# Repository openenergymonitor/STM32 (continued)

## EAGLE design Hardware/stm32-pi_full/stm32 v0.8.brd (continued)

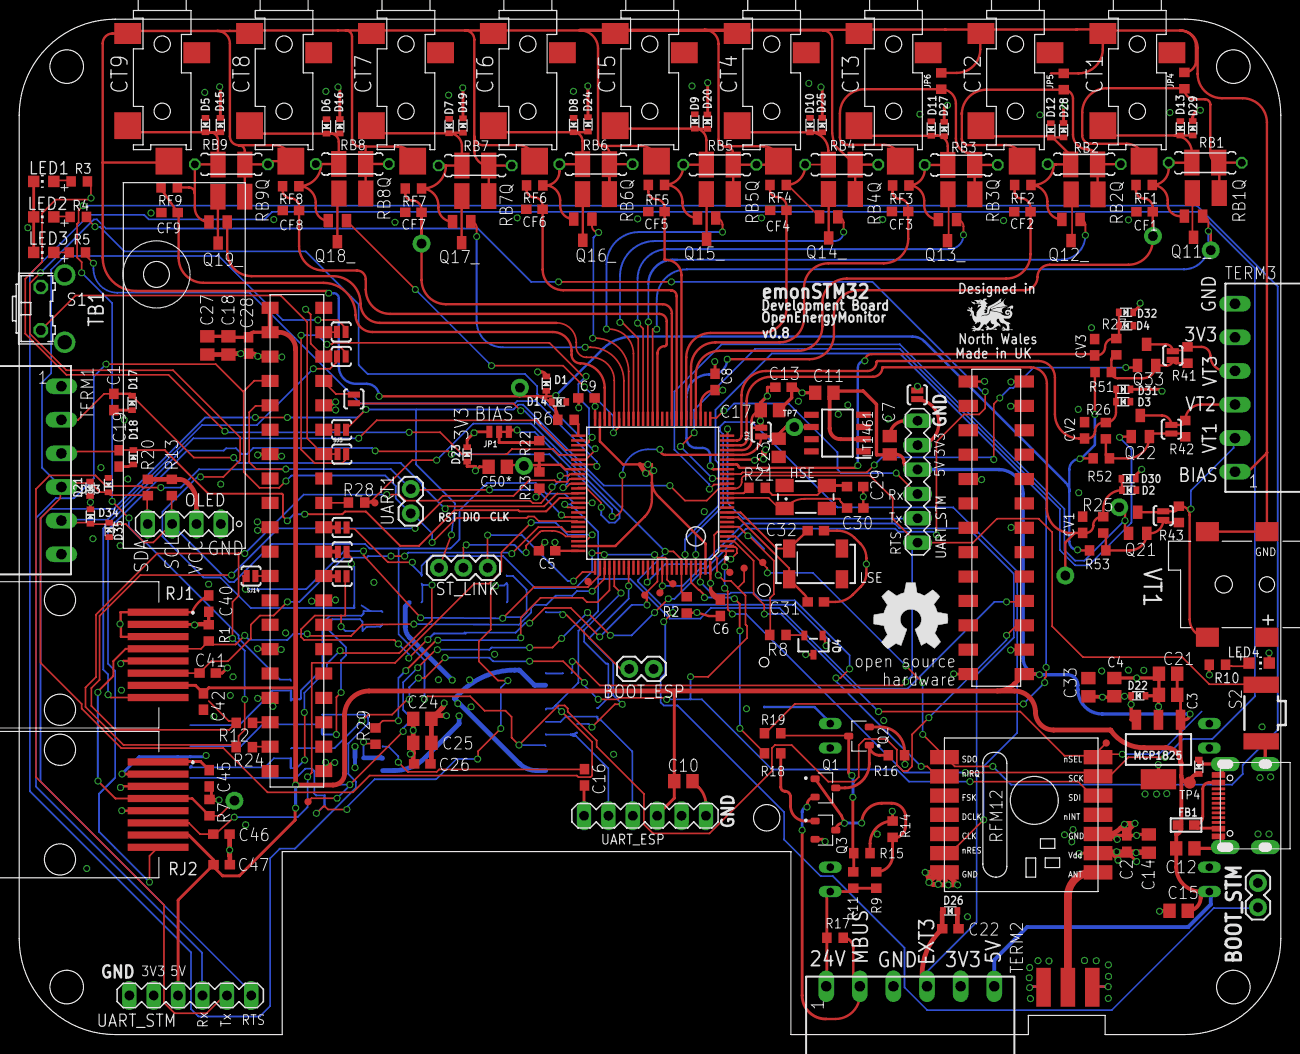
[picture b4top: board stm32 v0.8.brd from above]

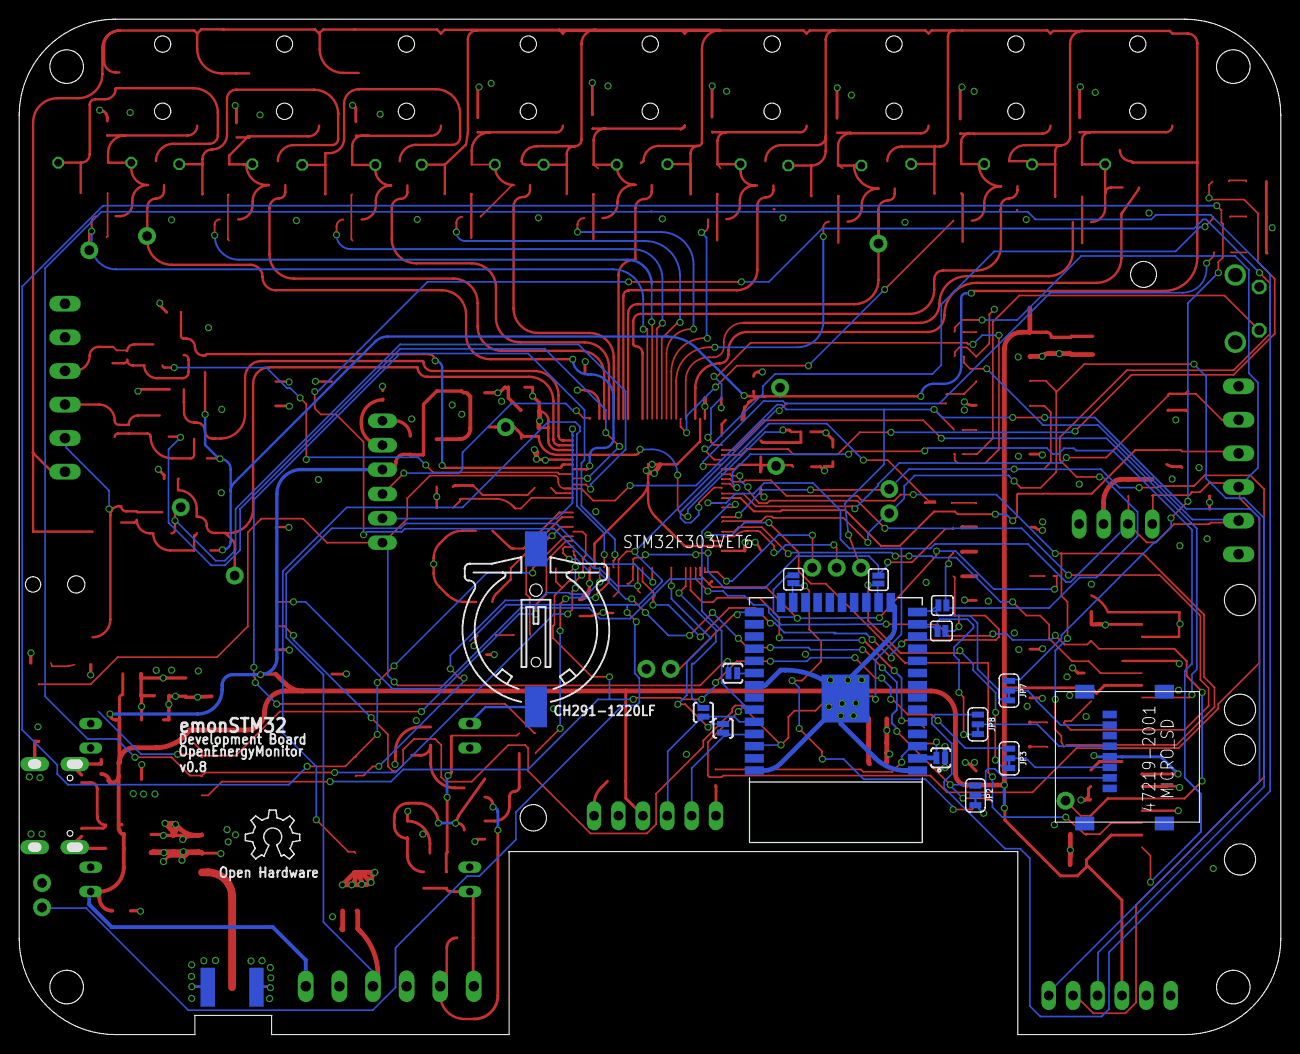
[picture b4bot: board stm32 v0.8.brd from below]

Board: 4 copper layers, 131.4 x 105.8 mm, 270 parts (16 on the bottom side), 147 nets.

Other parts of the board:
LOGO1: OSHW_LOGO_6MILX0200-NT; OSHW_6X200_NOTEXT

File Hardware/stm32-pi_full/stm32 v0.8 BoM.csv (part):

Part;Value;Device;Package;Description;ALLIED_NUMBER;ALLIED_PRICE-STOCK;AVAILABILITY;CREATED_BY;DESCRIPTION;DIGIKEY_PART_NUMBER;HEIGHT;MANUFACTURER;MANUFACTURER_NAME;MANUFACTURER_PART_NUMBER;MF;MOUSER_PART_NUMBER;MOUSER_PRICE-STOCK;MP;MPN;OC_FARNELL;OC_NEWARK;PACKAGE;POPULARITY;PRICE;PROD_ID;RS_PART_NUMBER;RS_PRICE-STOCK;SPICEPREFIX;TP_SIGNAL_NAME;VALUE
BOOT_ESP;;M02PTH;1X02;Header 2;;;;;;;;;;;;;;;;;;;;;;;;;;
BOOT_STM;;M02PTH;1X02;Header 2;;;;;;;;;;;;;;;;;;;;;;;;;;
C1;100nF;C-EUC0603;C0603;CAPACITOR, European symbol;;;;;;;;;;;;;;;;;;;;;;;;;;
C2;100nF;C-EUC0603;C0603;CAPACITOR, European symbol;;;;;;;;;;;;;;;;;;;;;;;;;;
C3;2.2uF;C-EUC0805;C0805;CAPACITOR, European symbol;;;;;;;;;;;;;;;;;;;88;;;;;C;;
C4;2.2uF;C-EUC0805;C0805;CAPACITOR, European symbol;;;;;;;;;;;;;;;;;;;88;;;;;C;;
C5;100nF;C-EUC0603;C0603;CAPACITOR, European symbol;;;;;;;;;;;;;;;;;;;;;;;;;;
C6;100nF;C-EUC0603;C0603;CAPACITOR, European symbol;;;;;;;;;;;;;;;;;;;;;;;;;;
C7;2.2uF;C-EUC0805;C0805;CAPACITOR, European symbol;;;;;;;;;;;;;;;;;;;88;;;;;C;;
C8;100nF;C-EUC0603;C0603;CAPACITOR, European symbol;;;;;;;;;;;;;;;;;;;;;;;;;;
C9;100nF;C-EUC0603;C0603;CAPACITOR, European symbol;;;;;;;;;;;;;;;;;;;;;;;;;;
C10;2.2uF;C-EUC0805;C0805;CAPACITOR, European symbol;;;;;;;;;;;;;;;;;;;88;;;;;C;;
C11;2.2uF;C-EUC0805;C0805;CAPACITOR, European symbol;;;;;;;;;;;;;;;;;;;88;;;;;C;;
C12;47uF;C-EUC0805;C0805;CAPACITOR, European symbol;;;;;;;;;;;;;;;;;;;88;;;;;C;;
C13;100nF;C-EUC0603;C0603;CAPACITOR, European symbol;;;;;;;;;;;;;;;;;;;73;;;;;C;;
C14;2.2uF;C-EUC0805;C0805;CAPACITOR, European symbol;;;;;;;;;;;;;;;;;;;88;;;;;C;;
C15;2.2uF;C-EUC0805;C0805;CAPACITOR, European symbol;;;;;;;;;;;;;;;;;;;88;;;;;C;;
C16;100nF;C-EUC0603;C0603;CAPACITOR, European symbol;;;;;;;;;;;;;;;;;;;;;;;;;;
C17;2.2uF;C-EUC0805;C0805;CAPACITOR, European symbol;;;;;;;;;;;;;;;;;;;88;;;;;C;;
C18;2.2uF;C-EUC0805;C0805;CAPACITOR, European symbol;;;;;;;;;;;;;;;;;;;88;;;;;C;;
C19;100nF;C-EUC0603;C0603;CAPACITOR, European symbol;;;;;;;;;;;;;;;;;;;;;;;;;;
C21;47uF;C-EUC0805;C0805;CAPACITOR, European symbol;;;;;;;;;;;;;;;;;;;88;;;;;C;;
C22;100nF;C-EUC0603;C0603;CAPACITOR, European symbol;;;;;;;;;;;;;;;;;;;;;;;;;;
C23;2.2uF;C-EUC0805;C0805;CAPACITOR, European symbol;;;;;;;;;;;;;;;;;;;88;;;;;C;;
C24;2.2uF;C-EUC0805;C0805;CAPACITOR, European symbol;;;;;;;;;;;;;;;;;;;88;;;;;C;;
C25;2.2uF;C-EUC0805;C0805;CAPACITOR, European symbol;;;;;;;;;;;;;;;;;;;88;;;;;C;;
C26;100nF;C-EUC0603;C0603;CAPACITOR, European symbol;;;;;;;;;;;;;;;;;;;;;;;;;;
C27;2.2uF;C-EUC0805;C0805;CAPACITOR, European symbol;;;;;;;;;;;;;;;;;;;88;;;;;C;;
C28;100nF;C-EUC0603;C0603;CAPACITOR, European symbol;;;;;;;;;;;;;;;;;;;;;;;;;;
C29;15pF;C-EUC0603;C0603;CAPACITOR, European symbol;;;;;;;;;;;;;;;;;;;73;;;;;C;;
C30;15pF;C-EUC0603;C0603;CAPACITOR, European symbol;;;;;;;;;;;;;;;;;;;73;;;;;C;;
C31;10pF;C-EUC0603;C0603;CAPACITOR, European symbol;;;;;;;;;;;;;;;;;;;88;;;;;C;;
C32;10pF;C-EUC0603;C0603;CAPACITOR, European symbol;;;;;;;;;;;;;;;;;;;88;;;;;C;;
C33;47uF;C-EUC0805;C0805;CAPACITOR, European symbol;;;;;;;;;;;;;;;;;;;88;;;;;C;;
C40;100nF;C-EUC0603;C0603;CAPACITOR, European symbol;;;;;;;;;;;;;;;;;;;;;;;;;;
C41;100nF;C-EUC0603;C0603;CAPACITOR, European symbol;;;;;;;;;;;;;;;;;;;;;;;;;;
C42;100nF;C-EUC0603;C0603;CAPACITOR, European symbol;;;;;;;;;;;;;;;;;;;;;;;;;;
C45;100nF;C-EUC0603;C0603;CAPACITOR, European symbol;;;;;;;;;;;;;;;;;;;;;;;;;;
C46;100nF;C-EUC0603;C0603;CAPACITOR, European symbol;;;;;;;;;;;;;;;;;;;;;;;;;;
C47;100nF;C-EUC0603;C0603;CAPACITOR, European symbol;;;;;;;;;;;;;;;;;;;;;;;;;;
C50*;2.2uF;C-EUC0805;C0805;CAPACITOR, European symbol;;;;;;;;;;;;;;;;;;;88;;;;;C;;
CF1;10nF;C-EUC0805;C0805;CAPACITOR, European symbol;;;;;;;;;;;;;;;;;;;;;;;;;;
CF2;10nF;C-EUC0805;C0805;CAPACITOR, European symbol;;;;;;;;;;;;;;;;;;;;;;;;;;
CF3;10nF;C-EUC0805;C0805;CAPACITOR, European symbol;;;;;;;;;;;;;;;;;;;;;;;;;;
CF4;10nF;C-EUC0805;C0805;CAPACITOR, European symbol;;;;;;;;;;;;;;;;;;;;;;;;;;
CF5;10nF;C-EUC0805;C0805;CAPACITOR, European symbol;;;;;;;;;;;;;;;;;;;;;;;;;;
CF6;10nF;C-EUC0805;C0805;CAPACITOR, European symbol;;;;;;;;;;;;;;;;;;;;;;;;;;
CF7;10nF;C-EUC0805;C0805;CAPACITOR, European symbol;;;;;;;;;;;;;;;;;;;;;;;;;;
CF8;10nF;C-EUC0805;C0805;CAPACITOR, European symbol;;;;;;;;;;;;;;;;;;;;;;;;;;
CF9;10nF;C-EUC0805;C0805;CAPACITOR, European symbol;;;;;;;;;;;;;;;;;;;;;;;;;;
CT1;SJ-3523-SMT;STEREO_SMD;STEREO_SMT;3.5mm Stereo Jack SMT;;;;;;;;;;;;;;;SJ-3523-SMT;;;;;;;;;;;
CT2;SJ-3523-SMT;STEREO_SMD;STEREO_SMT;3.5mm Stereo Jack SMT;;;;;;;;;;;;;;;SJ-3523-SMT;;;;;;;;;;;
CT3;SJ-3523-SMT;STEREO_SMD;STEREO_SMT;3.5mm Stereo Jack SMT;;;;;;;;;;;;;;;SJ-3523-SMT;;;;;;;;;;;
CT4;SJ-3523-SMT;STEREO_SMD;STEREO_SMT;3.5mm Stereo Jack SMT;;;;;;;;;;;;;;;SJ-3523-SMT;;;;;;;;;;;
CT5;SJ-3523-SMT;STEREO_SMD;STEREO_SMT;3.5mm Stereo Jack SMT;;;;;;;;;;;;;;;SJ-3523-SMT;;;;;;;;;;;
CT6;SJ-3523-SMT;STEREO_SMD;STEREO_SMT;3.5mm Stereo Jack SMT;;;;;;;;;;;;;;;SJ-3523-SMT;;;;;;;;;;;
CT7;SJ-3523-SMT;STEREO_SMD;STEREO_SMT;3.5mm Stereo Jack SMT;;;;;;;;;;;;;;;SJ-3523-SMT;;;;;;;;;;;
CT8;SJ-3523-SMT;STEREO_SMD;STEREO_SMT;3.5mm Stereo Jack SMT;;;;;;;;;;;;;;;SJ-3523-SMT;;;;;;;;;;;
CT9;SJ-3523-SMT;STEREO_SMD;STEREO_SMT;3.5mm Stereo Jack SMT;;;;;;;;;;;;;;;SJ-3523-SMT;;;;;;;;;;;
CV1;10nF;C-EUC0805;C0805;CAPACITOR, European symbol;;;;;;;;;;;;;;;;;;;;;;;;;;
CV2;10nF;C-EUC0805;C0805;CAPACITOR, European symbol;;;;;;;;;;;;;;;;;;;;;;;;;;
CV3;10nF;C-EUC0805;C0805;CAPACITOR, European symbol;;;;;;;;;;;;;;;;;;;;;;;;;;
D1;ESD5Z3.3T1G;DIODESOD-523;SOD-523;Diode;;;;;;;;;;;;;;;;;;;;;;;;;;
D2;ESD5Z3.3T1G;DIODESOD-523;SOD-523;Diode;;;;;;;;;;;;;;;;;;;;;;;;;;
D3;ESD5Z3.3T1G;DIODESOD-523;SOD-523;Diode;;;;;;;;;;;;;;;;;;;;;;;;;;
D4;ESD5Z3.3T1G;DIODESOD-523;SOD-523;Diode;;;;;;;;;;;;;;;;;;;;;;;;;;
D5;ESD5Z3.3T1G;DIODESOD-523;SOD-523;Diode;;;;;;;;;;;;;;;;;;;;;;;;;;
D6;ESD5Z3.3T1G;DIODESOD-523;SOD-523;Diode;;;;;;;;;;;;;;;;;;;;;;;;;;
D7;ESD5Z3.3T1G;DIODESOD-523;SOD-523;Diode;;;;;;;;;;;;;;;;;;;;;;;;;;
D8;ESD5Z3.3T1G;DIODESOD-523;SOD-523;Diode;;;;;;;;;;;;;;;;;;;;;;;;;;
D9;ESD5Z3.3T1G;DIODESOD-523;SOD-523;Diode;;;;;;;;;;;;;;;;;;;;;;;;;;
D10;ESD5Z3.3T1G;DIODESOD-523;SOD-523;Diode;;;;;;;;;;;;;;;;;;;;;;;;;;
D11;ESD5Z3.3T1G;DIODESOD-523;SOD-523;Diode;;;;;;;;;;;;;;;;;;;;;;;;;;
D12;ESD5Z3.3T1G;DIODESOD-523;SOD-523;Diode;;;;;;;;;;;;;;;;;;;;;;;;;;
D13;ESD5Z3.3T1G;DIODESOD-523;SOD-523;Diode;;;;;;;;;;;;;;;;;;;;;;;;;;
D14;ESD5Z3.3T1G;DIODESOD-523;SOD-523;Diode;;;;;;;;;;;;;;;;;;;;;;;;;;
D15;ESD5Z3.3T1G;DIODESOD-523;SOD-523;Diode;;;;;;;;;;;;;;;;;;;;;;;;;;
D16;ESD5Z3.3T1G;DIODESOD-523;SOD-523;Diode;;;;;;;;;;;;;;;;;;;;;;;;;;
D17;ESD5Z3.3T1G;DIODESOD-523;SOD-523;Diode;;;;;;;;;;;;;;;;;;;;;;;;;;
D18;ESD5Z3.3T1G;DIODESOD-523;SOD-523;Diode;;;;;;;;;;;;;;;;;;;;;;;;;;
D19;ESD5Z3.3T1G;DIODESOD-523;SOD-523;Diode;;;;;;;;;;;;;;;;;;;;;;;;;;
D20;ESD5Z3.3T1G;DIODESOD-523;SOD-523;Diode;;;;;;;;;;;;;;;;;;;;;;;;;;
D21;ESD5Z3.3T1G;DIODESOD-523;SOD-523;Diode;;;;;;;;;;;;;;;;;;;;;;;;;;
D22;ESD5Z3.3T1G;DIODESOD-523;SOD-523;Diode;;;;;;;;;;;;;;;;;;;;;;;;;;
D23;ESD5Z3.3T1G;DIODESOD-523;SOD-523;Diode;;;;;;;;;;;;;;;;;;;;;;;;;;
D24;ESD5Z3.3T1G;DIODESOD-523;SOD-523;Diode;;;;;;;;;;;;;;;;;;;;;;;;;;
D25;ESD5Z3.3T1G;DIODESOD-523;SOD-523;Diode;;;;;;;;;;;;;;;;;;;;;;;;;;
D26;ESD5Z3.3T1G;DIODESOD-523;SOD-523;Diode;;;;;;;;;;;;;;;;;;;;;;;;;;
D27;ESD5Z3.3T1G;DIODESOD-523;SOD-523;Diode;;;;;;;;;;;;;;;;;;;;;;;;;;
D28;ESD5Z3.3T1G;DIODESOD-523;SOD-523;Diode;;;;;;;;;;;;;;;;;;;;;;;;;;
D29;ESD5Z3.3T1G;DIODESOD-523;SOD-523;Diode;;;;;;;;;;;;;;;;;;;;;;;;;;
D30;ESD5Z3.3T1G;DIODESOD-523;SOD-523;Diode;;;;;;;;;;;;;;;;;;;;;;;;;;
D31;ESD5Z3.3T1G;DIODESOD-523;SOD-523;Diode;;;;;;;;;;;;;;;;;;;;;;;;;;
D32;ESD5Z3.3T1G;DIODESOD-523;SOD-523;Diode;;;;;;;;;;;;;;;;;;;;;;;;;;
D33;ESD5Z3.3T1G;DIODESOD-523;SOD-523;Diode;;;;;;;;;;;;;;;;;;;;;;;;;;
D34;ESD5Z3.3T1G;DIODESOD-523;SOD-523;Diode;;;;;;;;;;;;;;;;;;;;;;;;;;
D35;ESD5Z3.3T1G;DIODESOD-523;SOD-523;Diode;;;;;;;;;;;;;;;;;;;;;;;;;;
D40*1;ESD5Z5.0T1G;DIODESOD-523;SOD-523;Diode;;;;;;;;;;;;;;;;;;;;;;;;;;
EXPANSION;TSM-113-01-T-DV;PINHD-2X13SMT;2X13_SMT;PIN HEADER;;;;;;;;;;;;;;;;;;;;;;;;;;
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
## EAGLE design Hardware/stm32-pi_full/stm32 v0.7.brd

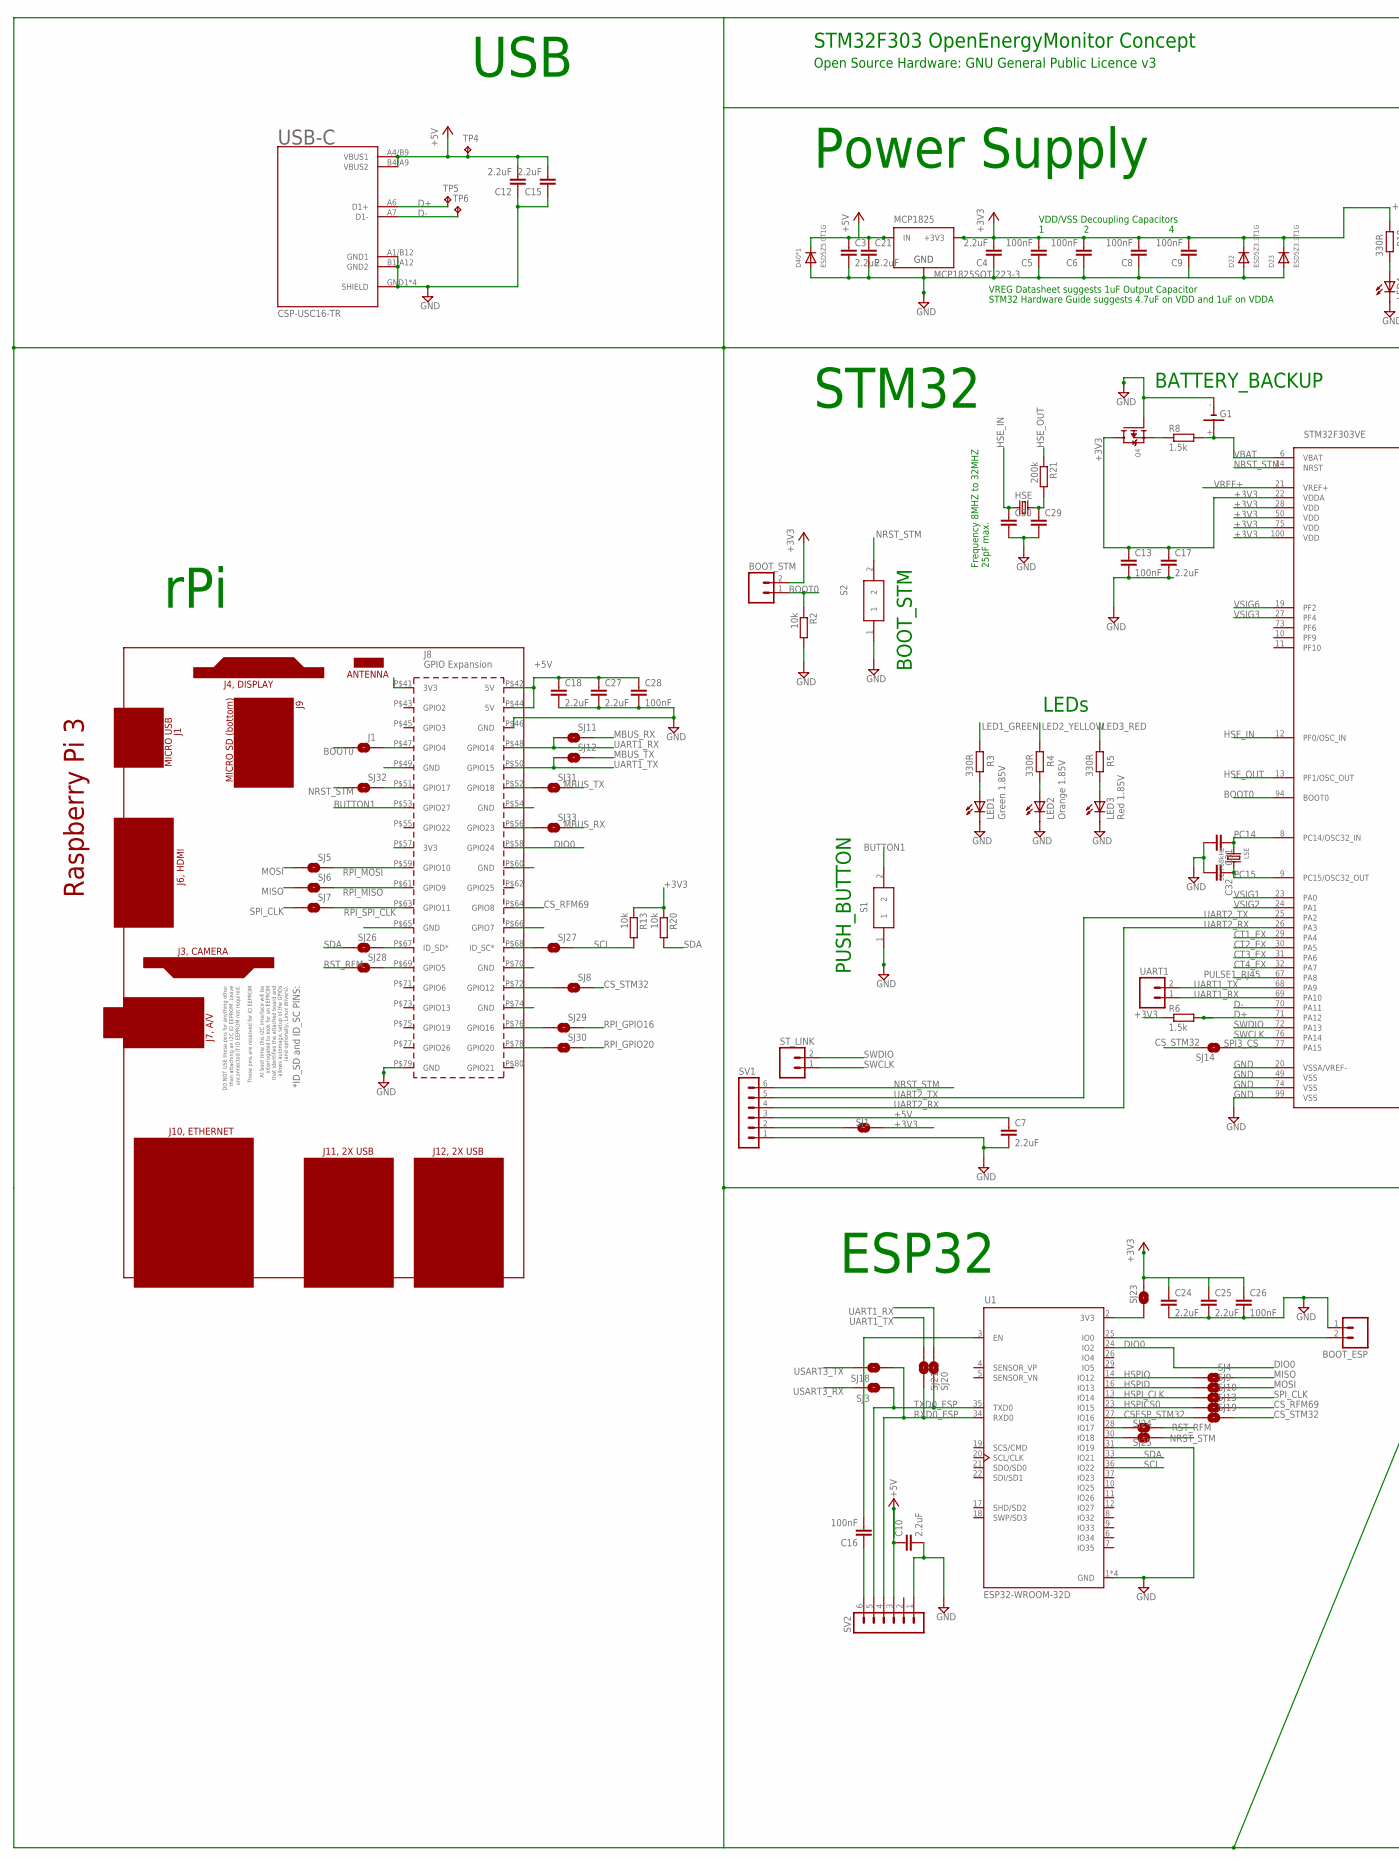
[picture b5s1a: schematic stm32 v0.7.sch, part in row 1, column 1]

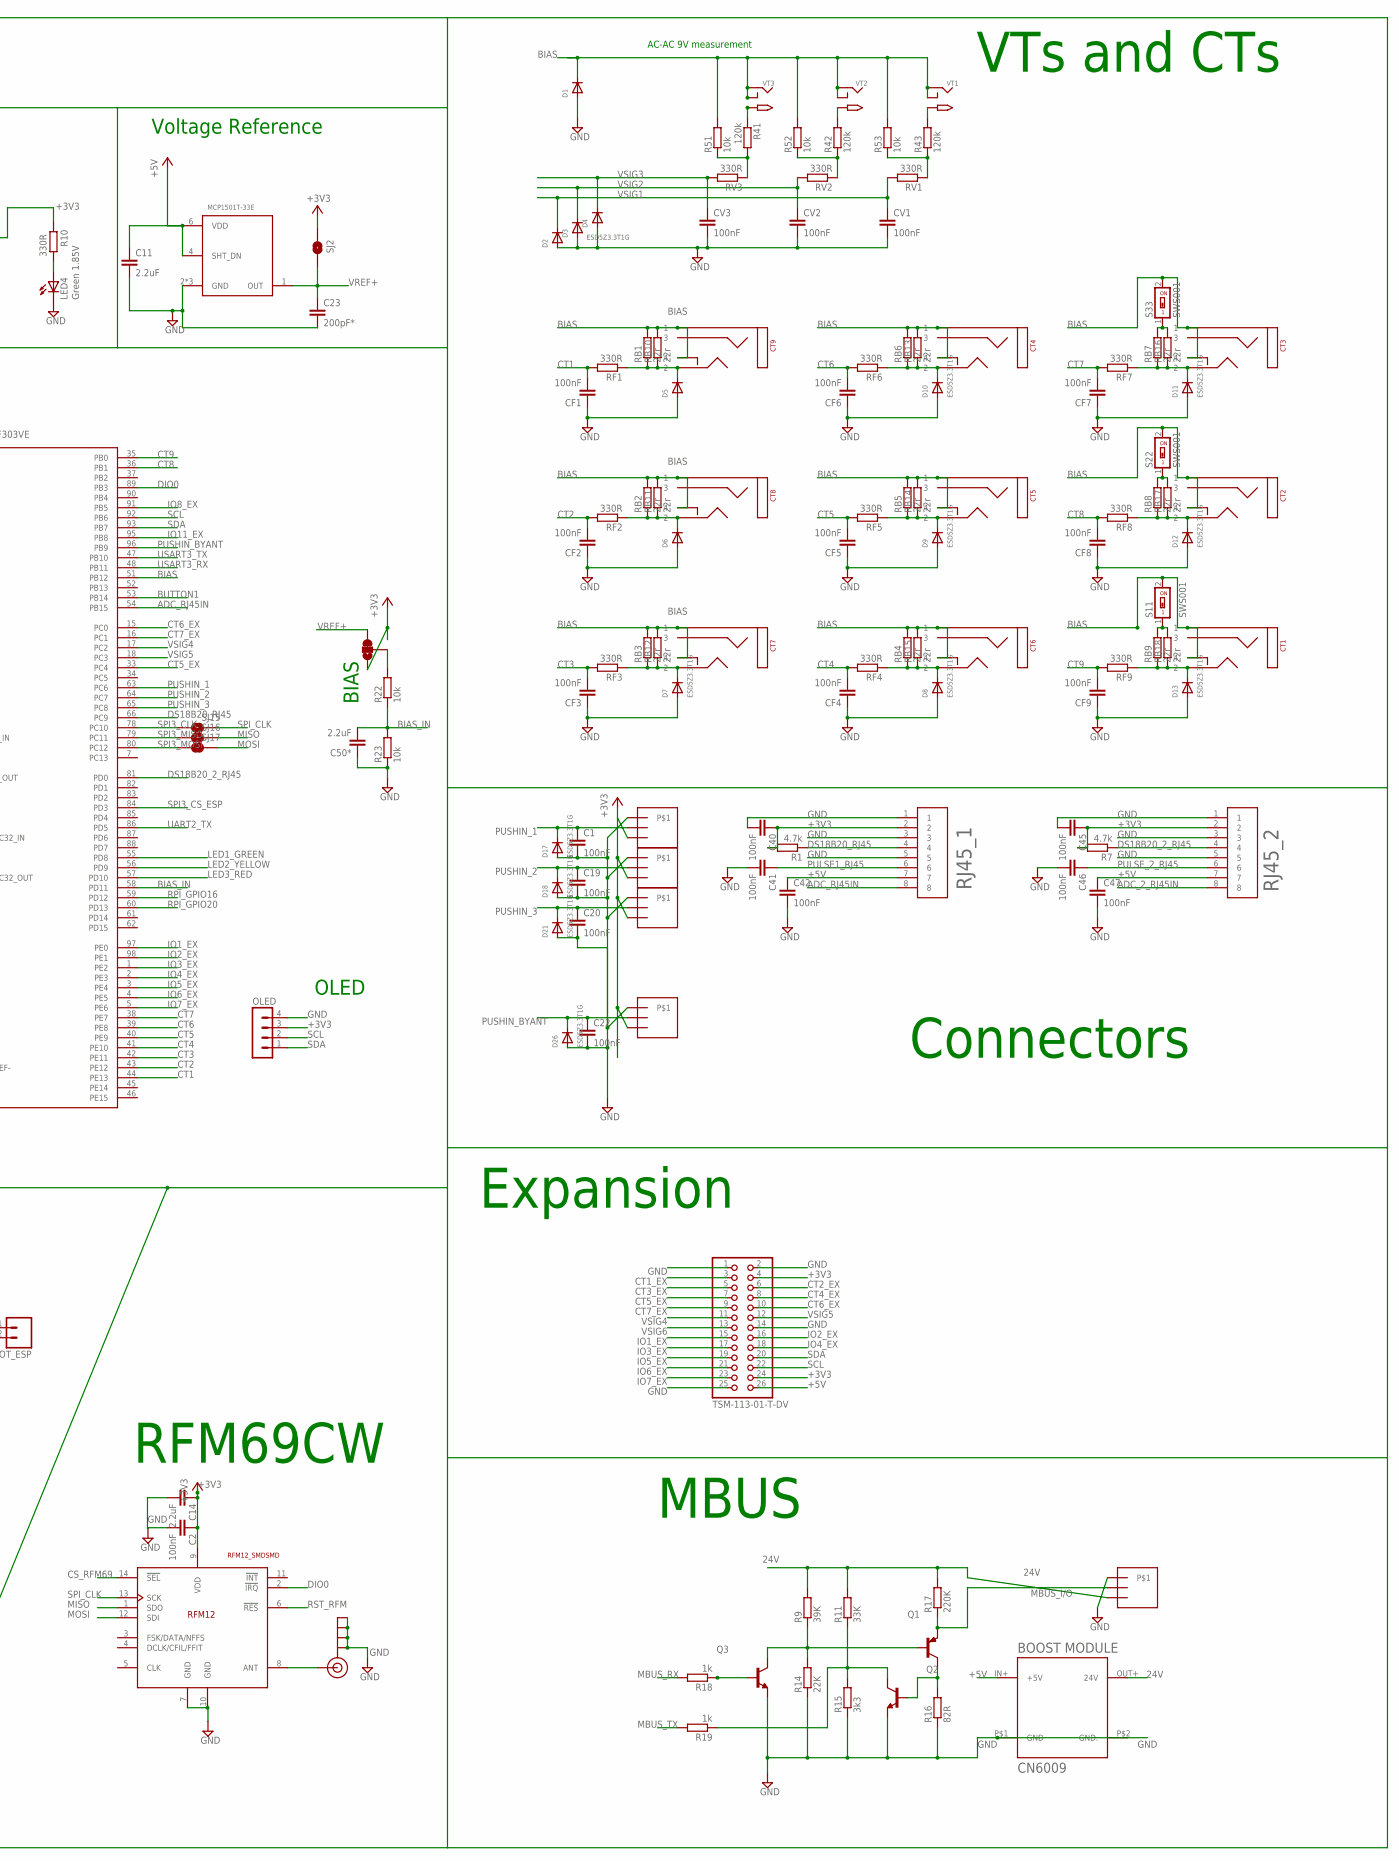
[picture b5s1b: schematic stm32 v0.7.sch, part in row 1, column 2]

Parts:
BOOT_ESP: M02PTH; 1X02
BOOT_STM: M02PTH; 1X02
C1, C2, C5, C6, C8, C9, C13, C16, C19, C20, C22, C26, C28, C40, C41, C42, C45, C46, C47: 100nF; C0603
C3, C4, C7, C10, C11, C12, C14, C15, C17, C18, C21, C24, C25, C27, C31, C32, C50*: 2.2uF; C0805
C23: 200pF*; C0603
C29, C30: 5nF; C0603
CF1, CF2, CF3, CF4, CF5, CF6, CF7, CF8, CF9: 100nF; C0603
CT1, CT2, CT3, CT4, CT5, CT6, CT7, CT8, CT9: SJ-3523-SMT; STEREO_SMT; MPN SJ-3523-SMT
CV1, CV2, CV3: 100nF; C0603
D1, D2, D3, D4, D5, D6, D7, D8, D9, D10, D11, D12, D13, D17, D18, D21, D22, D23, D26: ESD5Z3.3T1G; SOD-523
D40*1: ESD5Z5.0T1G; SOD-523
EXPANSION: TSM-113-01-T-DV; 2X13_SMT
G1: CH291-1220LF
HSE: 406C35E08M00000; CTS406
J1: SOLDERJUMPERNO; SJ_2S-NO
J$1: SMA_EDGE; SMA-EDGE
JP1: JUMPER-SMT_3_1-NC_TRACE_NO-SILK; SMT-JUMPER_3_1-NC_TRACE_NO-SILK
LED1, LED4: Green 1.85V; CHIP-LED0805
LED2: Orange 1.85V; CHIP-LED0805
LED3: Red 1.85V; CHIP-LED0805
LSE: 32.768kHz; CRYSTAL_8X3.8
MCP1825: MCP1825SOT-223-3; SOT-223
OLED: MA04-1-OLEDOLED; MA04-1-OLED
PCB2: TSM-120-01-T-DV; RPI3MIRROR2
Q1: MMBT3906; SOT23
Q2, Q3: MMBT3904; SOT23
Q4: MOSFET-P; SOT23-R
R1, R7: 4.7k; R0603
R2, R13, R20, R22, R23, R51, R52, R53: 10k; R0603
R3, R4, R5, R10: 330R; R0603
R6, R8: 1.5k; R0603
R9: 39K; R0603
R11: 33K; R0603
R14: 22K; R0603
R15: 3k3; R0603
R16: 82R; R0603
R17: 220K; R0603
R18, R19: 1k; R0603
R21: 200k; R0603
R41, R42, R43: 120k; R0603
RB1, RB2, RB3, RB4, RB5, RB6, RB7, RB8, RB9: 22r; R1206
RB10, RB11, RB12, RB13, RB14, RB15, RB16, RB17, RB18: 22r; 0207/7
RF1, RF2, RF3, RF4, RF5, RF6, RF7, RF8, RF9: 330R; R0603
RFM69HCW: RFM12_SMDSMD; RFM12
RJ45_1, RJ45_2: 95501-6889; 955016889
RV1, RV2, RV3: 330R; R0603
S1, S2: KSS221GLFS; KSS
S11, S22, S33: SWS001; SMS-001
SJ1, SJ2, SJ3, SJ4, SJ5, SJ6, SJ7, SJ8, SJ9, SJ10, SJ11, SJ12, SJ13, SJ14, SJ15, SJ16, SJ17, SJ18, SJ19, SJ20, SJ21, SJ23, SJ24, SJ25, SJ26, SJ27, SJ28, SJ29, SJ30, SJ31, SJ32, SJ33: SOLDERJUMPERNO; SJ_2S-NO
STM32F303VE: STM32F303VE; TQFP100
ST_LINK: M02PTH; 1X02
SV1, SV2: MA06-1
TP4, TP5, TP6: TPB1,27; B1,27
U1: ESP32-WROOM-32D; MODULE_ESP32-WROOM-32D
U$1, U$3, U$4, U$5, U$6: 3.5MM_TERMINAL_BLOCK; 3.5MM_X3
U$2: BOOST_MODULE; BOOST
UART1: M02PTH; 1X02
USB-C: CSP-USC16-TR; USB-C
VREF_3V3: MCP1501T-33E; SOT95P280X145-6N
VT1, VT2, VT3: ADC-028-2-T; DCJACK_2MM_SMT; MPN ADC-028-1-T

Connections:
24V: R9.2, R11.2, R17.2, U$2.OUT+ (24V), U$6.P$1
+3V3: BOOT_STM.2, C2.1, C4.2, C5.2, C6.2, C8.2, C9.2, C13.1, C14.1, C17.1, C24.1, C25.1, C26.1, C40.1, C45.1, D22.K (C), D23.K (C), EXPANSION.4, EXPANSION.24, JP1.1, MCP1825.3 (+3V3), OLED.3, Q4.3 (D), R1.2, R6.1, R7.2, R10.2, R13.1, R20.1, RFM69HCW.9 (VDD), RJ45_1.2, RJ45_2.2, SJ1.2, SJ2.1, SJ23.2, STM32F303VE.22 (VDDA), STM32F303VE.28 (VDD), STM32F303VE.50 (VDD), STM32F303VE.75 (VDD), STM32F303VE.100 (VDD), U$1.P$1, U$3.P$1, U$4.P$1, U$5.P$1
+3V3_ESP: SJ23.1, U1.2 (3V3)
+5V: C3.1, C7.1, C10.1, C11.1, C12.2, C15.2, C18.1, C21.1, C27.1, C28.1, C42.1, C47.1, D40*1.K (C), EXPANSION.26, MCP1825.1 (IN), PCB2.P$42 (5V), PCB2.P$44 (5V), RJ45_1.7, RJ45_2.7, SV1.3, SV2.3, TP4.TP, U$2.IN+ (+5V), USB-C.A4/B9 (VBUS1), USB-C.B4/A9 (VBUS2), VREF_3V3.4 (SHT_DN), VREF_3V3.6 (VDD)
AC1: R43.2, VT1.PWR2 (TIP)
AC2: R42.2, VT2.PWR2 (TIP)
AC3: R41.1, VT3.PWR2 (TIP)
ADC0: R41.2, R51.1, RV3.1
ADC_2_RJ45IN: RJ45_2.8
ADC_RJ45IN: RJ45_1.8, STM32F303VE.54 (PB15)
ANT: J$1.SIG (SIGNAL), RFM69HCW.8 (ANT)
BIAS: CT1.P$1 (1), CT1.P$4 (4), CT2.P$1 (1), CT2.P$4 (4), CT3.P$1 (1), CT3.P$4 (4), CT4.P$1 (1), CT4.P$4 (4), CT5.P$1 (1), CT5.P$4 (4), CT6.P$1 (1), CT6.P$4 (4), CT7.P$1 (1), CT7.P$4 (4), CT8.P$1 (1), CT8.P$4 (4), CT9.P$1 (1), CT9.P$4 (4), D1.K (C), R51.2, R52.2, R53.2, RB1.2, RB2.2, RB3.2, RB4.2, RB5.2, RB6.2, RB10.2, RB11.2, RB12.2, RB13.2, RB14.2, RB15.2, S11.2, S22.2, S33.2, STM32F303VE.51 (PB12), VT1.GND (RING), VT1.GNDBREAK (RING_SW), VT2.GND (RING), VT2.GNDBREAK (RING_SW), VT3.GND (RING), VT3.GNDBREAK (RING_SW)
BIAS_IN: C50*.2, R22.1, R23.2, STM32F303VE.58 (PD11)
BOOT0: BOOT_STM.1, J1.1, R2.1, STM32F303VE.94 (BOOT0)
BOOT0_RPI: J1.2, PCB2.P$47 (GPIO4)
BUTTON1: PCB2.P$53 (GPIO27), S1.2, STM32F303VE.53 (PB14)
CSESP_STM32: SJ19.1, U1.27 (IO16)
CS_RFM69: PCB2.P$64 (GPIO8), RFM69HCW.14 (!SEL), SJ13.2
CS_STM32: SJ8.2, SJ14.1, SJ19.2
CS_STM32_RPI: PCB2.P$72 (GPIO12), SJ8.1
CT1: CF1.2, RF1.2, STM32F303VE.44 (PE13)
CT1_EX: EXPANSION.3, STM32F303VE.29 (PA4)
CT2: CF2.2, RF2.2, STM32F303VE.43 (PE12)
CT2_EX: EXPANSION.6, STM32F303VE.30 (PA5)
CT3: CF3.2, RF3.2, STM32F303VE.42 (PE11)
CT3_EX: EXPANSION.5, STM32F303VE.31 (PA6)
CT4: CF4.2, RF4.2, STM32F303VE.41 (PE10)
CT4_EX: EXPANSION.8, STM32F303VE.32 (PA7)
CT5: CF5.2, RF5.2, STM32F303VE.40 (PE9)
CT5_EX: EXPANSION.7, STM32F303VE.33 (PC4)
CT6: CF6.2, RF6.2, STM32F303VE.39 (PE8)
CT6_EX: EXPANSION.10, STM32F303VE.15 (PC0)
CT7: CF7.2, RF7.2, STM32F303VE.38 (PE7)
CT7_EX: EXPANSION.9, STM32F303VE.16 (PC1)
CT8: CF8.2, RF8.2, STM32F303VE.36 (PB1)
CT9: CF9.2, RF9.2, STM32F303VE.35 (PB0)
D+: R6.2, STM32F303VE.71 (PA12), TP5.TP, USB-C.A6 (D1+)
D-: STM32F303VE.70 (PA11), TP6.TP, USB-C.A7 (D1-)
DIO0: PCB2.P$58 (GPIO24), RFM69HCW.2 (!IRQ), STM32F303VE.89 (PB3), U1.24 (IO2)
DS18B20_2_RJ45: R7.1, RJ45_2.4, STM32F303VE.81 (PD0)
DS18B20_RJ45: R1.1, RJ45_1.4, STM32F303VE.66 (PC9)
GND: BOOT_ESP.1, C1.2, C2.2, C3.2, C4.1, C5.1, C6.1, C7.2, C8.1, C9.1, C10.2, C11.2, C12.1, C13.2, C14.2, C15.1, C17.2, C18.2, C19.2, C20.2, C21.2, C22.2, C23.2, C24.2, C25.2, C26.2, C27.2, C28.2, C29.2, C30.2, C31.2, C32.2, C40.2, C41.2, C42.2, C45.2, C46.2, C47.2, C50*.1, CF1.1, CF2.1, CF3.1, CF4.1, CF5.1, CF6.1, CF7.1, CF8.1, CF9.1, CV1.2, CV2.2, CV3.2, D1.A, D2.A, D3.A, D4.A, D5.A, D6.A, D7.A, D8.A, D9.A, D10.A, D11.A, D12.A, D13.A, D17.A, D18.A, D21.A, D22.A, D23.A, D26.A, D40*1.A, EXPANSION.1, EXPANSION.2, EXPANSION.14, EXPANSION.25, G1.-, J$1.GND@0 (GND), J$1.GND@1 (GND), J$1.GND@2 (GND), J$1.GND@3 (GND), LED1.C, LED2.C, LED3.C, LED4.C, MCP1825.2 (GND), MCP1825.4 (GND), OLED.4, PCB2.P$46 (GND), PCB2.P$49 (GND), PCB2.P$54 (GND), PCB2.P$60 (GND), PCB2.P$65 (GND), PCB2.P$70 (GND), PCB2.P$74 (GND), PCB2.P$79 (GND), Q2.2 (E), Q3.2 (E), Q4.1 (G), R2.2, R14.1, R15.1, R16.1, R23.1, RFM69HCW.7 (GND), RFM69HCW.10 (GND), RJ45_1.1, RJ45_1.3, RJ45_1.5, RJ45_2.1, RJ45_2.3, RJ45_2.5, S1.1, S2.1, STM32F303VE.20 (VSSA/VREF-), STM32F303VE.49 (VSS), STM32F303VE.74 (VSS), STM32F303VE.99 (VSS), SV1.1, SV2.1, U1.1 (GND), U1.15 (GND), U1.31 (IO19), U1.38 (GND), U1.39 (GND), U$1.P$3, U$2.P$1 (GND), U$2.P$2 (GND.), U$3.P$3, U$4.P$3, U$5.P$3, U$6.P$3, USB-C.A1/B12 (GND1), USB-C.B1/A12 (GND2), USB-C.GND1 (SHIELD), USB-C.GND2 (SHIELD), USB-C.GND3 (SHIELD), USB-C.GND4 (SHIELD), VREF_3V3.2 (GND), VREF_3V3.3 (GND), VREF_3V3.5 (GND)
HSE_IN: C30.1, HSE.1, STM32F303VE.12 (PF0/OSC_IN)
HSE_OUT: R21.1, STM32F303VE.13 (PF1/OSC_OUT)
HSE_OUT_: C29.1, HSE.3 (2), R21.2
HSPICS0: SJ13.1, U1.23 (IO15)
HSPID: SJ9.1, U1.16 (IO13)
HSPIQ: SJ4.1, U1.14 (IO12)
HSPI_CLK: SJ10.1, U1.13 (IO14)
IO1_EX: EXPANSION.15, STM32F303VE.97 (PE0)
IO2_EX: EXPANSION.16, STM32F303VE.98 (PE1)
IO3_EX: EXPANSION.17, STM32F303VE.1 (PE2)
IO4_EX: EXPANSION.18, STM32F303VE.2 (PE3)
IO5_EX: EXPANSION.19, STM32F303VE.3 (PE4)
IO6_EX: EXPANSION.21, STM32F303VE.4 (PE5)
IO7_EX: EXPANSION.23, STM32F303VE.5 (PE6)
IO8_EX: STM32F303VE.91 (PB5)
IO11_EX: STM32F303VE.95 (PB8)
LED1_GREEN: R3.2, STM32F303VE.55 (PD8)
LED2_YELLOW: R4.2, STM32F303VE.56 (PD9)
LED3_RED: R5.2, STM32F303VE.57 (PD10)
MBUS_I/O: Q1.2 (E), R17.1, U$6.P$2
MBUS_RX: R18.2, SJ11.2, SJ33.2
MBUS_RX_RPI: PCB2.P$56 (GPIO23), SJ33.1
MBUS_TX: R19.2, SJ12.2, SJ31.2
MBUS_TX_RPI: PCB2.P$52 (GPIO18), SJ31.1
MISO: RFM69HCW.1 (SDO), SJ4.2, SJ6.1, SJ16.2
MOSI: RFM69HCW.12 (SDI), SJ5.1, SJ9.2, SJ17.2
unnamed: SJ1.1, SV1.2
unnamed: CT9.P$2 (2), D5.K (C), RB1.1, RB10.1, RF1.1
unnamed: LED2.A, R4.1
unnamed: LED3.A, R5.1
unnamed: CT8.P$2 (2), D6.K (C), RB2.1, RB11.1, RF2.1
unnamed: LED4.A, R10.1
unnamed: CT7.P$2 (2), D7.K (C), RB3.1, RB12.1, RF3.1
unnamed: JP1.2, R22.2
unnamed: C16.1, SV2.6
unnamed: C16.2, U1.3 (EN)
unnamed: Q4.2 (S), R8.1
unnamed: BOOT_ESP.2, U1.25 (IO0)
unnamed: RB9.2, RB18.2, S11.1
unnamed: RB8.2, RB17.2, S22.1
unnamed: RB7.2, RB16.2, S33.1
unnamed: Q1.3 (C), Q2.1 (B), R16.2
unnamed: Q1.1 (B), Q3.3 (C), R9.1, R14.2
unnamed: Q2.3 (C), R11.1, R15.2, R19.1
unnamed: Q3.1 (B), R18.1
unnamed: R42.1, R52.1, RV2.1
unnamed: R43.1, R53.1, RV1.1
unnamed: CT6.P$2 (2), D8.K (C), RB4.1, RB15.1, RF4.1
unnamed: CT5.P$2 (2), D9.K (C), RB5.1, RB14.1, RF5.1
unnamed: CT4.P$2 (2), D10.K (C), RB6.1, RB13.1, RF6.1
unnamed: LED1.A, R3.1
unnamed: CT3.P$2 (2), D11.K (C), RB7.1, RB16.1, RF7.1
unnamed: CT2.P$2 (2), D12.K (C), RB8.1, RB17.1, RF8.1
unnamed: CT1.P$2 (2), D13.K (C), RB9.1, RB18.1, RF9.1
NRST_STM: S2.2, SJ25.2, SJ32.1, STM32F303VE.14 (NRST), SV1.6
NRST_STM_ESP: SJ25.1, U1.30 (IO18)
NRST_STM_RPI: PCB2.P$51 (GPIO17), SJ32.2
PC14: C31.1, LSE.P$1 (1), STM32F303VE.8 (PC14/OSC32_IN)
PC15: C32.1, LSE.P$4 (2), STM32F303VE.9 (PC15/OSC32_OUT)
PULSE1_RJ45: C41.1, RJ45_1.6, STM32F303VE.67 (PA8)
PULSE_2_RJ45: C46.1, RJ45_2.6
PUSHIN_1: C1.1, D17.K (C), STM32F303VE.63 (PC6), U$1.P$2
PUSHIN_2: C19.1, D18.K (C), STM32F303VE.64 (PC7), U$3.P$2
PUSHIN_3: C20.1, D21.K (C), STM32F303VE.65 (PC8), U$4.P$2
PUSHIN_BYANT: C22.1, D26.K (C), STM32F303VE.96 (PB9), U$5.P$2
RPI_GPIO16: SJ29.2, STM32F303VE.59 (PD12)
RPI_GPIO16_RPI: PCB2.P$76 (GPIO16), SJ29.1
RPI_GPIO20: SJ30.2, STM32F303VE.60 (PD13)
RPI_GPIO20_RPI: PCB2.P$78 (GPIO20), SJ30.1
RPI_MISO: PCB2.P$61 (GPIO9), SJ6.2
RPI_MOSI: PCB2.P$59 (GPIO10), SJ5.2
RPI_SPI_CLK: PCB2.P$63 (GPIO11), SJ7.2
RST_RFM: RFM69HCW.6 (!RES), SJ24.2, SJ28.1
RST_RFM_ESP: SJ24.1, U1.28 (IO17)
RST_RFM_RPI: PCB2.P$69 (GPIO5), SJ28.2
RXD0_ESP: SJ18.1, SJ21.2, SV2.4, U1.34 (RXD0)
SCL: EXPANSION.22, OLED.2, R13.2, SJ27.2, STM32F303VE.92 (PB6), U1.36 (IO22)
SCL_RPI: PCB2.P$68 (ID_SC*), SJ27.1
SDA: EXPANSION.20, OLED.1, R20.2, SJ26.1, STM32F303VE.93 (PB7), U1.33 (IO21)
SDA_RPI: PCB2.P$67 (ID_SD*), SJ26.2
SPI3_CLK: SJ15.1, STM32F303VE.78 (PC10)
SPI3_CS: SJ14.2, STM32F303VE.77 (PA15)
SPI3_CS_ESP: STM32F303VE.84 (PD3)
SPI3_MISO: SJ16.1, STM32F303VE.79 (PC11)
SPI3_MOSI: SJ17.1, STM32F303VE.80 (PC12)
SPI_CLK: RFM69HCW.13 (SCK), SJ7.1, SJ10.2, SJ15.2
SWCLK: STM32F303VE.76 (PA14), ST_LINK.1
SWDIO: STM32F303VE.72 (PA13), ST_LINK.2
TXD0_ESP: SJ3.1, SJ20.2, SV2.5, U1.35 (TXD0)
UART1_RX: PCB2.P$48 (GPIO14), SJ11.1, SJ20.1, STM32F303VE.69 (PA10), UART1.1
UART1_TX: PCB2.P$50 (GPIO15), SJ12.1, SJ21.1, STM32F303VE.68 (PA9), UART1.2
UART2_RX: STM32F303VE.26 (PA3), SV1.4
UART2_TX: STM32F303VE.25 (PA2), STM32F303VE.86 (PD5), SV1.5
USART3_RX: SJ3.2, STM32F303VE.48 (PB11)
USART3_TX: SJ18.2, STM32F303VE.47 (PB10)
VBAT: G1.+, R8.2, STM32F303VE.6 (VBAT)
VREF+: C23.1, JP1.3, SJ2.2, STM32F303VE.21 (VREF+), VREF_3V3.1 (OUT)
VSIG1: CV1.1, D2.K (C), RV1.2, STM32F303VE.23 (PA0)
VSIG2: CV2.1, D3.K (C), RV2.2, STM32F303VE.24 (PA1)
VSIG3: CV3.1, D4.K (C), RV3.2, STM32F303VE.27 (PF4)
VSIG4: EXPANSION.11, STM32F303VE.17 (PC2)
VSIG5: EXPANSION.12, STM32F303VE.18 (PC3)
VSIG6: EXPANSION.13, STM32F303VE.19 (PF2)

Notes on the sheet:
VDD/VSS Decoupling Capacitors
VREG Datasheet suggests 1uF Output Capacitor
STM32 Hardware Guide suggests 4.7uF on VDD and 1uF on VDDA
AC-AC 9V measurement
VTs and CTs
STM32F303 OpenEnergyMonitor Concept
Power Supply
STM32
Open Source Hardware: GNU General Public Licence v3
Frequency 8MHZ to 32MHZ 25pF max.
Voltage Reference
ESP32
MBUS
rPi
BOOT_STM
RFM69CW
Connectors
Expansion
LEDs
PUSH_BUTTON
OLED
BIAS
USB
BATTERY_BACKUP

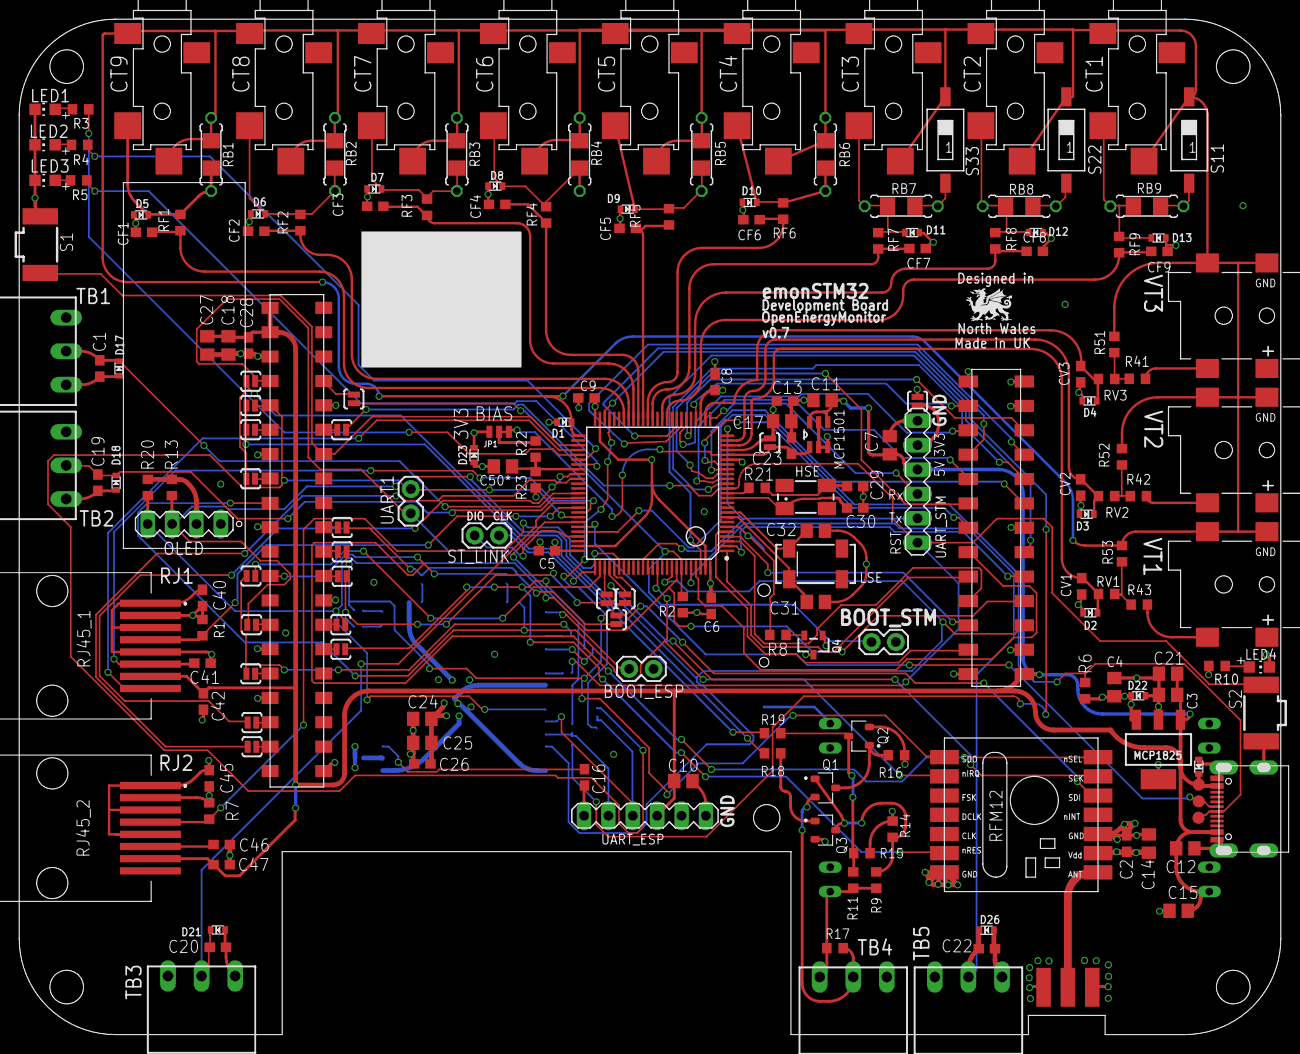
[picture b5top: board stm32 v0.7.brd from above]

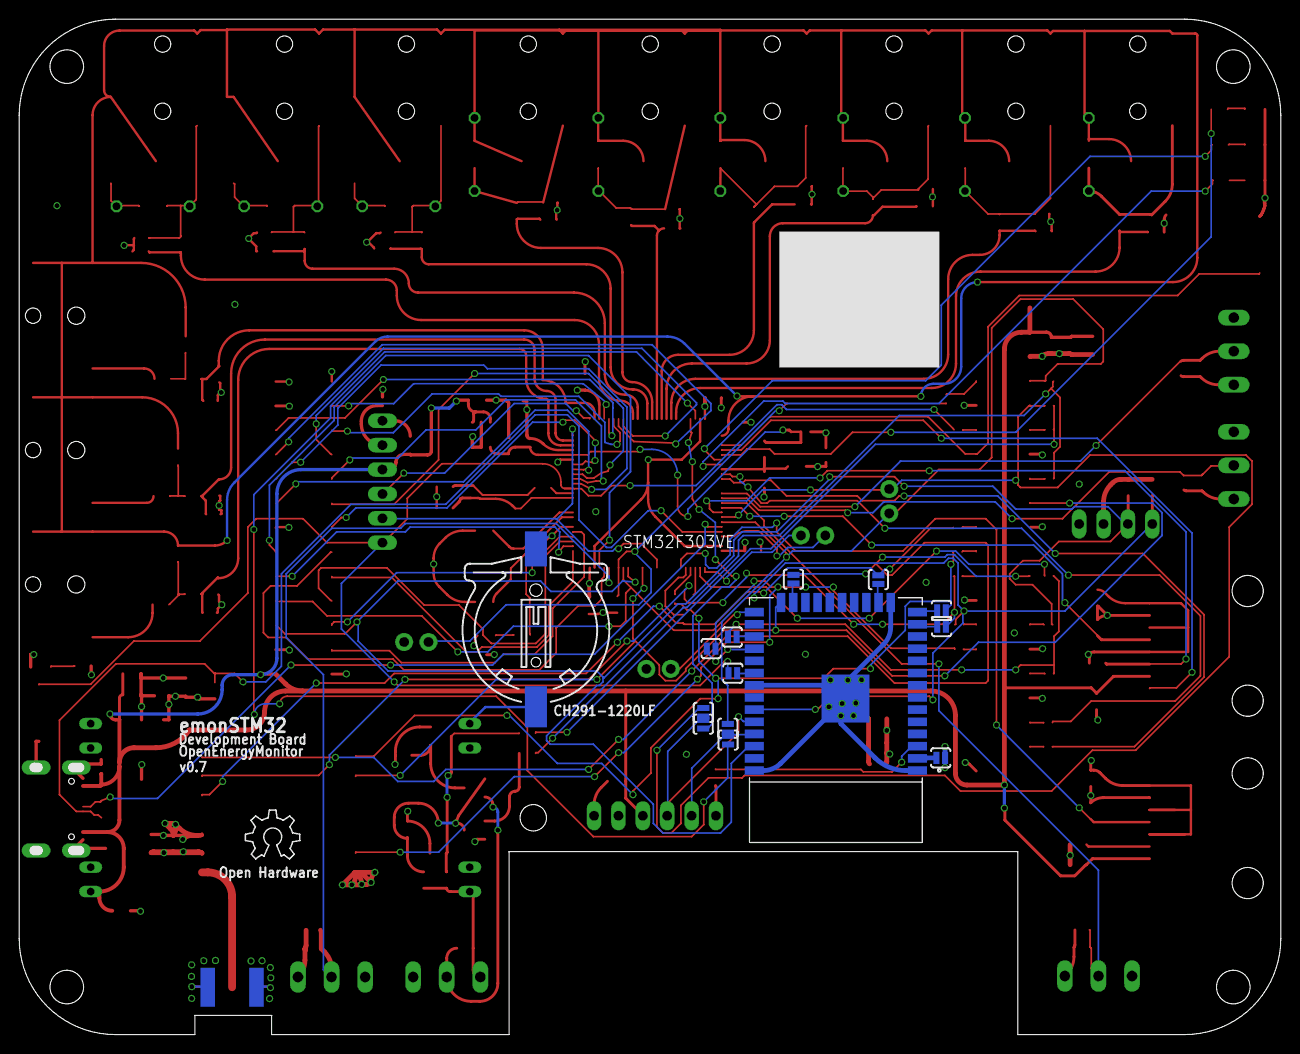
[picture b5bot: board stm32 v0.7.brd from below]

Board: 4 copper layers, 131.4 x 105.8 mm, 219 parts (15 on the bottom side), 141 nets.

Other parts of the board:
LOGO1: OSHW_LOGO_6MILX0200-NT; OSHW_6X200_NOTEXT
